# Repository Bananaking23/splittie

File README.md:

# splittie
I am going to design a board about 18.5x18.5mm in size, it will include leds, kailh switches and diodes, and i am going to create a split keyboard with it.

I made this project because every now and then i get the urge to create a new maccropad/keyboard with this pcb, i can create it in any shape or form and it is MUCH easier to wire then a handwired keyboard.
## Schematic

## Pcb

## Case

## BOM

| Part | Quantity | Price | Total price | Notes | Link |
|------|----------|-------|-------------|-------|------|
| PCB | | 17.02 | 18.52 | | [JLCPCB](https://jlcpcb.com) |
| Switches | 58 | 12.14 | 12.14 | | [AliExpress](https://www.aliexpress.com/item/1005006068116422.html) |
| Hotswap sockets | 58 | 5.92 | 5.92 | | [AliExpress](https://www.aliexpress.com/item/1005012056973371.html) |
| SK6812 MINI-E | 58 | 3.26 | 3.26 | optional | [AliExpress](https://www.aliexpress.com/item/1005005186515165.html) |
| Diodes | 58 | 1.15 | 1.15 | | [AliExpress](https://www.aliexpress.com/item/1005007160563285.html) |
| Keycaps | 1 set | 10.09 | 10.09 | | [AliExpress](https://www.aliexpress.com/item/1005011935100353.html) |
| RP2040 Pro Micro | 2 | 2.03 | 4.06 | | [AliExpress](https://www.aliexpress.com/item/1005009890367599.html) |
| 0.91" OLED | 2 | 2.07 | 2.07 | | [AliExpress](https://www.aliexpress.com/item/1005008640108394.html) |
| EC11 | 2 | 1.52 | 1.52 | | [AliExpress](https://www.aliexpress.com/item/1005007644083514.html) |
| USB-C female | 2 | 1.11 | 1.11 | connect 2 halves together | [AliExpress](https://www.aliexpress.com/item/1005008529430881.html) |
| USB-C cable | 1 | 3.19 | 3.19 | connect 2 halves together | [AliExpress](https://www.aliexpress.com/item/1005008570336761.html) |
| **Total** | | **63.03** | **77.72** | | |

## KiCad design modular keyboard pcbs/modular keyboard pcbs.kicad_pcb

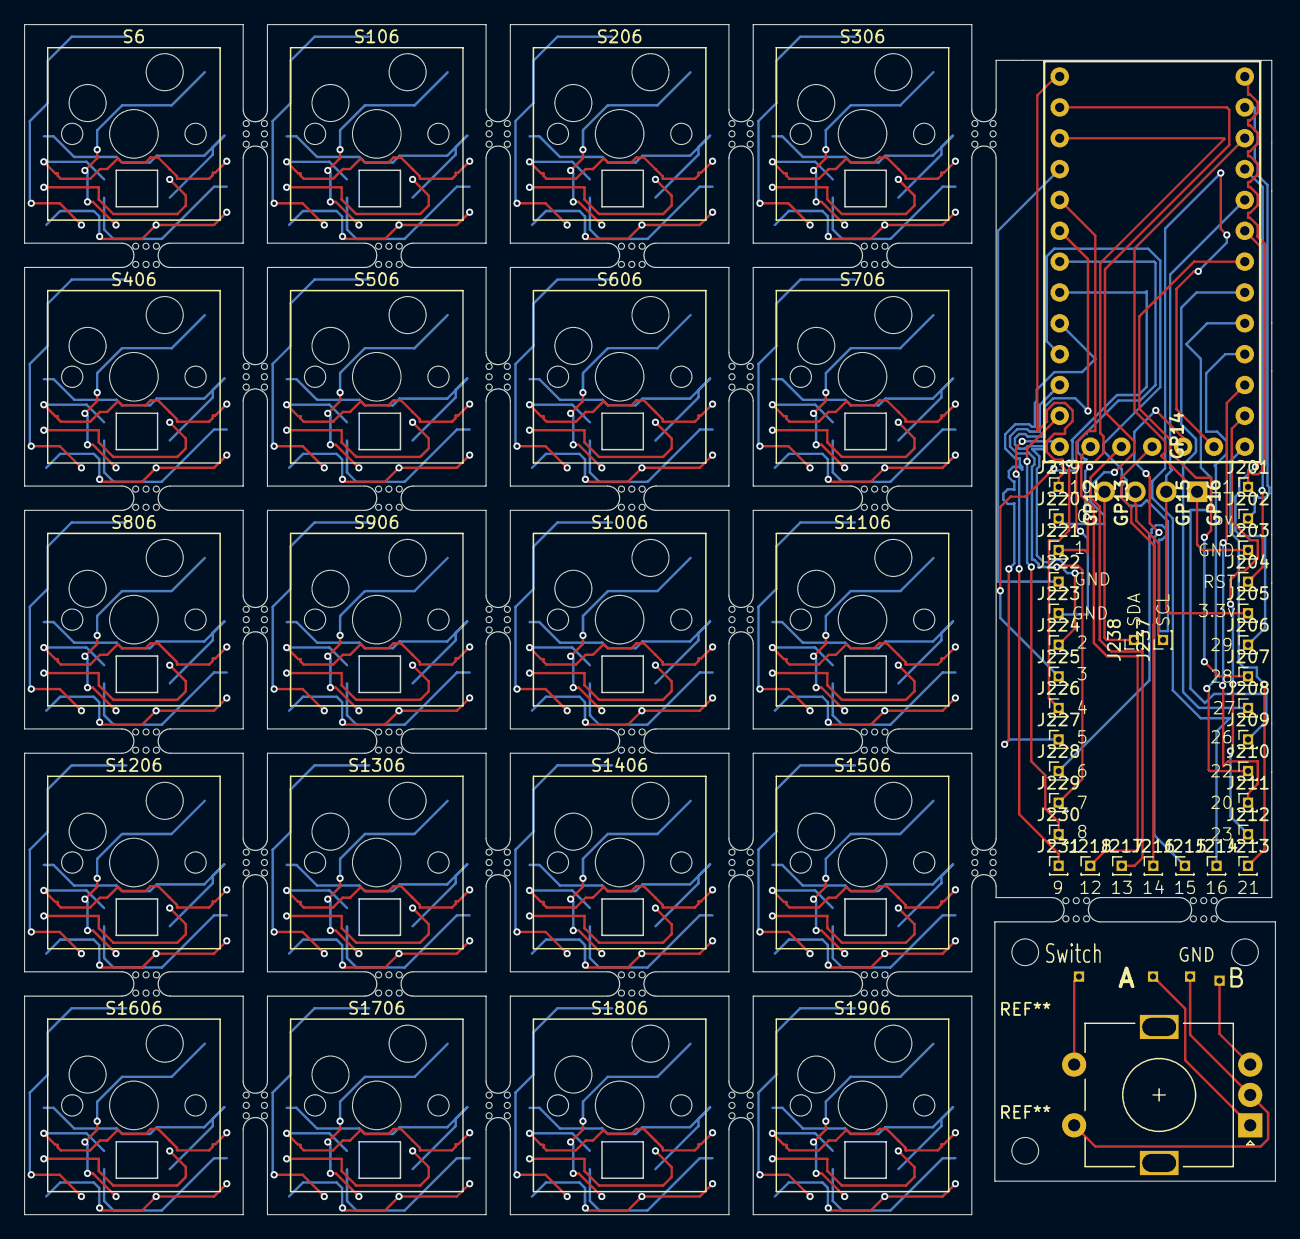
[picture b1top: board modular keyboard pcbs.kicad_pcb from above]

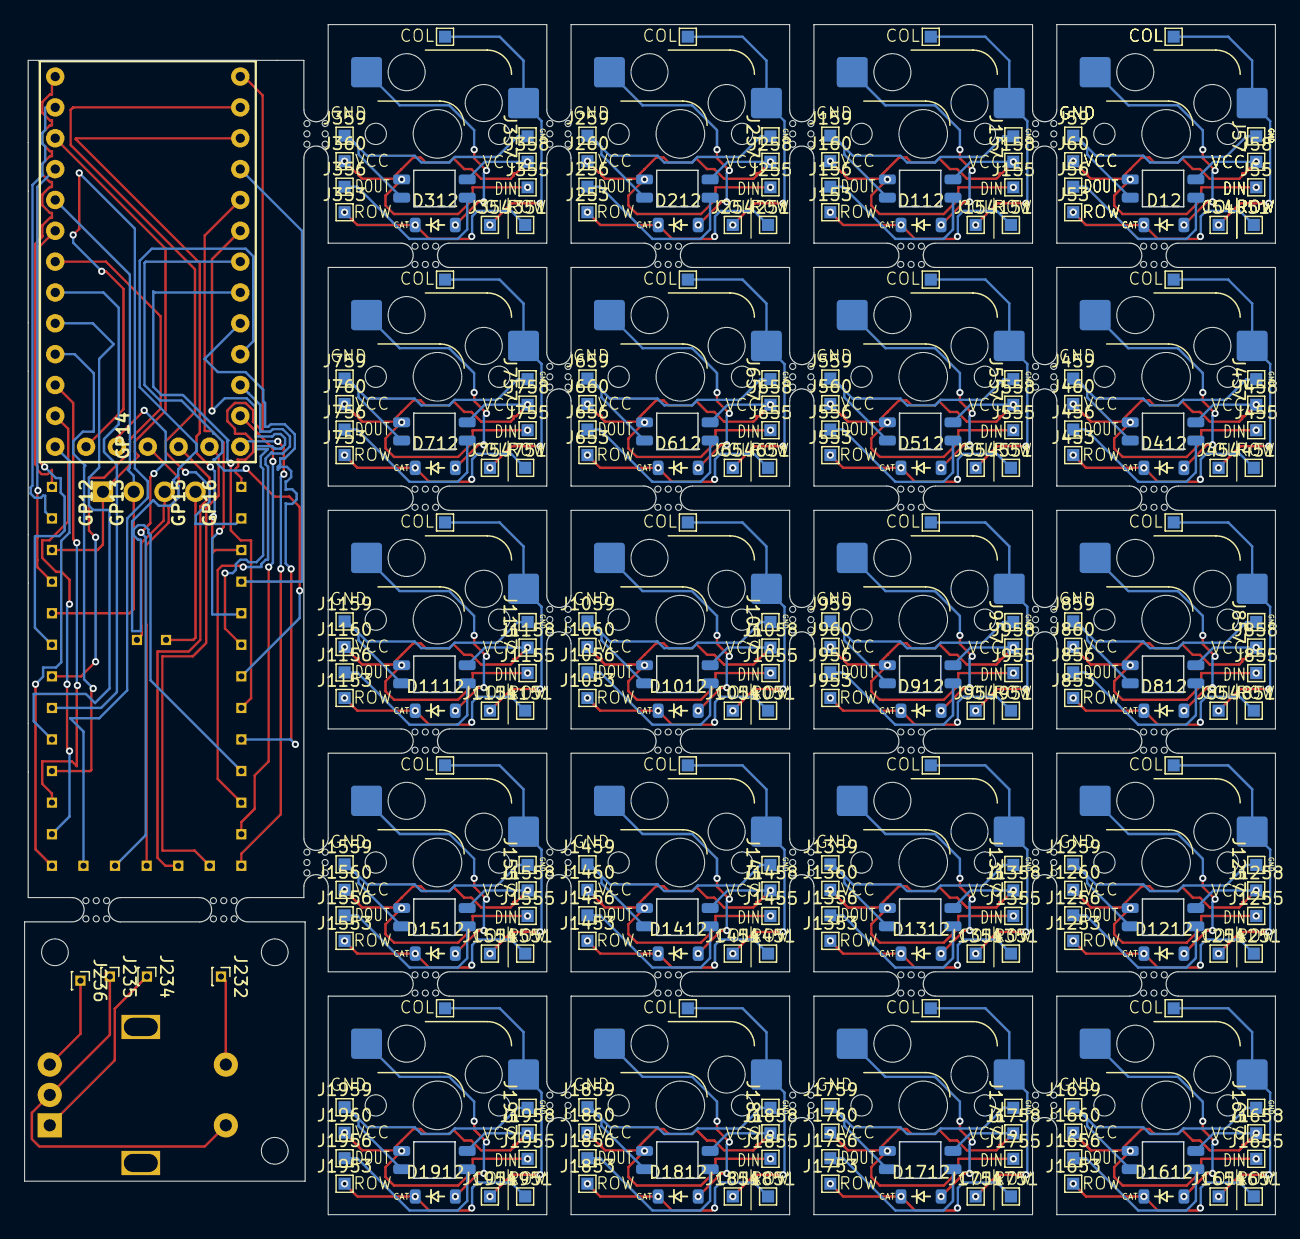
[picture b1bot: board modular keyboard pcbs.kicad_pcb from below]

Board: 2 copper layers, 103.0 x 98.0 mm, 300 parts (244 on the bottom side), 177 nets.

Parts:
D11, D111, D211, D311, D411, D511, D611, D711, D811, D911, D1011, D1111, D1211, D1311, D1411, D1511, D1611, D1711, D1811, D1911: LED_SK6812MINI
D12, D112, D212, D312, D412, D512, D612, D712, D812, D912, D1012, D1112, D1212, D1312, D1412, D1512, D1612, D1712, D1812, D1912: Diode_SOD-123
J51, J53, J151, J153, J251, J253, J351, J353, J451, J453, J551, J553, J651, J653, J751, J753, J851, J853, J951, J953, J1051, J1053, J1151, J1153, J1251, J1253, J1351, J1353, J1451, J1453, J1551, J1553, J1651, J1653, J1751, J1753, J1851, J1853, J1951, J1953: ROW; TestPoint_Pad_1.0x1.0mm
J52, J54, J152, J154, J252, J254, J352, J354, J452, J454, J552, J554, J652, J654, J752, J754, J852, J854, J952, J954, J1052, J1054, J1152, J1154, J1252, J1254, J1352, J1354, J1452, J1454, J1552, J1554, J1652, J1654, J1752, J1754, J1852, J1854, J1952, J1954: COL; TestPoint_Pad_1.0x1.0mm
J55, J155, J255, J355, J455, J555, J655, J755, J855, J955, J1055, J1155, J1255, J1355, J1455, J1555, J1655, J1755, J1855, J1955: DIN; TestPoint_Pad_1.0x1.0mm
J56, J156, J256, J356, J456, J556, J656, J756, J856, J956, J1056, J1156, J1256, J1356, J1456, J1556, J1656, J1756, J1856, J1956: DOUT; TestPoint_Pad_1.0x1.0mm
J57, J59, J157, J159, J257, J259, J357, J359, J457, J459, J557, J559, J657, J659, J757, J759, J857, J859, J957, J959, J1057, J1059, J1157, J1159, J1257, J1259, J1357, J1359, J1457, J1459, J1557, J1559, J1657, J1659, J1757, J1759, J1857, J1859, J1957, J1959: GND; TestPoint_Pad_1.0x1.0mm
J58, J60, J158, J160, J258, J260, J358, J360, J458, J460, J558, J560, J658, J660, J758, J760, J858, J860, J958, J960, J1058, J1060, J1158, J1160, J1258, J1260, J1358, J1360, J1458, J1460, J1558, J1560, J1658, J1660, J1758, J1760, J1858, J1860, J1958, J1960: VCC; TestPoint_Pad_1.0x1.0mm
J201, J202, J203, J204, J205, J206, J207, J208, J209, J210, J211, J212, J213, J214, J215, J216, J217, J218, J219, J220, J221, J222, J223, J224, J225, J226, J227, J228, J229, J230, J231, J232, J234, J235, J236, J237, J238: Conn_01x01_Pin; PinHeader_1x01_P1.00mm_Vertical
J233: OLED_128x32
S6, S106, S206, S306, S406, S506, S606, S706, S806, S906, S1006, S1106, S1206, S1306, S1406, S1506, S1606, S1706, S1806, S1906: Hotswap_MX_1.00u
SW1: RotaryEncoder_Switch; RotaryEncoder_Alps_EC11E-Switch_Vertical_H20mm
U1: RP2040_Pro_Micro

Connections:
/Cell r0c1/COL: J152.1, J154.1, S106.1
/Cell r0c1/DIN: D111.4 (DIN), J155.1
/Cell r0c1/DOUT: D111.2 (DOUT), J156.1
/Cell r0c1/GND: D111.3 (VSS), J157.1, J159.1
/Cell r0c1/Net-(D12-A): D112.2 (A), S106.2
/Cell r0c1/ROW: D112.1 (K), J151.1, J153.1
/Cell r0c1/VCC: D111.1 (VDD), J158.1, J160.1
/Cell r0c2/COL: J252.1, J254.1, S206.1
/Cell r0c2/DIN: D211.4 (DIN), J255.1
/Cell r0c2/DOUT: D211.2 (DOUT), J256.1
/Cell r0c2/GND: D211.3 (VSS), J257.1, J259.1
/Cell r0c2/Net-(D12-A): D212.2 (A), S206.2
/Cell r0c2/ROW: D212.1 (K), J251.1, J253.1
/Cell r0c2/VCC: D211.1 (VDD), J258.1, J260.1
/Cell r0c3/COL: J352.1, J354.1, S306.1
/Cell r0c3/DIN: D311.4 (DIN), J355.1
/Cell r0c3/DOUT: D311.2 (DOUT), J356.1
/Cell r0c3/GND: D311.3 (VSS), J357.1, J359.1
/Cell r0c3/Net-(D12-A): D312.2 (A), S306.2
/Cell r0c3/ROW: D312.1 (K), J351.1, J353.1
/Cell r0c3/VCC: D311.1 (VDD), J358.1, J360.1
/Cell r1c0/COL: J452.1, J454.1, S406.1
/Cell r1c0/DIN: D411.4 (DIN), J455.1
/Cell r1c0/DOUT: D411.2 (DOUT), J456.1
/Cell r1c0/GND: D411.3 (VSS), J457.1, J459.1
/Cell r1c0/Net-(D12-A): D412.2 (A), S406.2
/Cell r1c0/ROW: D412.1 (K), J451.1, J453.1
/Cell r1c0/VCC: D411.1 (VDD), J458.1, J460.1
/Cell r1c1/COL: J552.1, J554.1, S506.1
/Cell r1c1/DIN: D511.4 (DIN), J555.1
/Cell r1c1/DOUT: D511.2 (DOUT), J556.1
/Cell r1c1/GND: D511.3 (VSS), J557.1, J559.1
/Cell r1c1/Net-(D12-A): D512.2 (A), S506.2
/Cell r1c1/ROW: D512.1 (K), J551.1, J553.1
/Cell r1c1/VCC: D511.1 (VDD), J558.1, J560.1
/Cell r1c2/COL: J652.1, J654.1, S606.1
/Cell r1c2/DIN: D611.4 (DIN), J655.1
/Cell r1c2/DOUT: D611.2 (DOUT), J656.1
/Cell r1c2/GND: D611.3 (VSS), J657.1, J659.1
/Cell r1c2/Net-(D12-A): D612.2 (A), S606.2
/Cell r1c2/ROW: D612.1 (K), J651.1, J653.1
/Cell r1c2/VCC: D611.1 (VDD), J658.1, J660.1
/Cell r1c3/COL: J752.1, J754.1, S706.1
/Cell r1c3/DIN: D711.4 (DIN), J755.1
/Cell r1c3/DOUT: D711.2 (DOUT), J756.1
/Cell r1c3/GND: D711.3 (VSS), J757.1, J759.1
/Cell r1c3/Net-(D12-A): D712.2 (A), S706.2
/Cell r1c3/ROW: D712.1 (K), J751.1, J753.1
/Cell r1c3/VCC: D711.1 (VDD), J758.1, J760.1
/Cell r2c0/COL: J852.1, J854.1, S806.1
/Cell r2c0/DIN: D811.4 (DIN), J855.1
/Cell r2c0/DOUT: D811.2 (DOUT), J856.1
/Cell r2c0/GND: D811.3 (VSS), J857.1, J859.1
/Cell r2c0/Net-(D12-A): D812.2 (A), S806.2
/Cell r2c0/ROW: D812.1 (K), J851.1, J853.1
/Cell r2c0/VCC: D811.1 (VDD), J858.1, J860.1
/Cell r2c1/COL: J952.1, J954.1, S906.1
/Cell r2c1/DIN: D911.4 (DIN), J955.1
/Cell r2c1/DOUT: D911.2 (DOUT), J956.1
/Cell r2c1/GND: D911.3 (VSS), J957.1, J959.1
/Cell r2c1/Net-(D12-A): D912.2 (A), S906.2
/Cell r2c1/ROW: D912.1 (K), J951.1, J953.1
/Cell r2c1/VCC: D911.1 (VDD), J958.1, J960.1
/Cell r2c2/COL: J1052.1, J1054.1, S1006.1
/Cell r2c2/DIN: D1011.4 (DIN), J1055.1
/Cell r2c2/DOUT: D1011.2 (DOUT), J1056.1
/Cell r2c2/GND: D1011.3 (VSS), J1057.1, J1059.1
/Cell r2c2/Net-(D12-A): D1012.2 (A), S1006.2
/Cell r2c2/ROW: D1012.1 (K), J1051.1, J1053.1
/Cell r2c2/VCC: D1011.1 (VDD), J1058.1, J1060.1
/Cell r2c3/COL: J1152.1, J1154.1, S1106.1
/Cell r2c3/DIN: D1111.4 (DIN), J1155.1
/Cell r2c3/DOUT: D1111.2 (DOUT), J1156.1
/Cell r2c3/GND: D1111.3 (VSS), J1157.1, J1159.1
/Cell r2c3/Net-(D12-A): D1112.2 (A), S1106.2
/Cell r2c3/ROW: D1112.1 (K), J1151.1, J1153.1
/Cell r2c3/VCC: D1111.1 (VDD), J1158.1, J1160.1
/Cell r3c0/COL: J1252.1, J1254.1, S1206.1
/Cell r3c0/DIN: D1211.4 (DIN), J1255.1
/Cell r3c0/DOUT: D1211.2 (DOUT), J1256.1
/Cell r3c0/GND: D1211.3 (VSS), J1257.1, J1259.1
/Cell r3c0/Net-(D12-A): D1212.2 (A), S1206.2
/Cell r3c0/ROW: D1212.1 (K), J1251.1, J1253.1
/Cell r3c0/VCC: D1211.1 (VDD), J1258.1, J1260.1
/Cell r3c1/COL: J1352.1, J1354.1, S1306.1
/Cell r3c1/DIN: D1311.4 (DIN), J1355.1
/Cell r3c1/DOUT: D1311.2 (DOUT), J1356.1
/Cell r3c1/GND: D1311.3 (VSS), J1357.1, J1359.1
/Cell r3c1/Net-(D12-A): D1312.2 (A), S1306.2
/Cell r3c1/ROW: D1312.1 (K), J1351.1, J1353.1
/Cell r3c1/VCC: D1311.1 (VDD), J1358.1, J1360.1
/Cell r3c2/COL: J1452.1, J1454.1, S1406.1
/Cell r3c2/DIN: D1411.4 (DIN), J1455.1
/Cell r3c2/DOUT: D1411.2 (DOUT), J1456.1
/Cell r3c2/GND: D1411.3 (VSS), J1457.1, J1459.1
/Cell r3c2/Net-(D12-A): D1412.2 (A), S1406.2
/Cell r3c2/ROW: D1412.1 (K), J1451.1, J1453.1
/Cell r3c2/VCC: D1411.1 (VDD), J1458.1, J1460.1
/Cell r3c3/COL: J1552.1, J1554.1, S1506.1
/Cell r3c3/DIN: D1511.4 (DIN), J1555.1
/Cell r3c3/DOUT: D1511.2 (DOUT), J1556.1
/Cell r3c3/GND: D1511.3 (VSS), J1557.1, J1559.1
/Cell r3c3/Net-(D12-A): D1512.2 (A), S1506.2
/Cell r3c3/ROW: D1512.1 (K), J1551.1, J1553.1
/Cell r3c3/VCC: D1511.1 (VDD), J1558.1, J1560.1
/Cell r4c0/COL: J1652.1, J1654.1, S1606.1
/Cell r4c0/DIN: D1611.4 (DIN), J1655.1
/Cell r4c0/DOUT: D1611.2 (DOUT), J1656.1
/Cell r4c0/GND: D1611.3 (VSS), J1657.1, J1659.1
/Cell r4c0/Net-(D12-A): D1612.2 (A), S1606.2
/Cell r4c0/ROW: D1612.1 (K), J1651.1, J1653.1
/Cell r4c0/VCC: D1611.1 (VDD), J1658.1, J1660.1
/Cell r4c1/COL: J1752.1, J1754.1, S1706.1
/Cell r4c1/DIN: D1711.4 (DIN), J1755.1
/Cell r4c1/DOUT: D1711.2 (DOUT), J1756.1
/Cell r4c1/GND: D1711.3 (VSS), J1757.1, J1759.1
/Cell r4c1/Net-(D12-A): D1712.2 (A), S1706.2
/Cell r4c1/ROW: D1712.1 (K), J1751.1, J1753.1
/Cell r4c1/VCC: D1711.1 (VDD), J1758.1, J1760.1
/Cell r4c2/COL: J1852.1, J1854.1, S1806.1
/Cell r4c2/DIN: D1811.4 (DIN), J1855.1
/Cell r4c2/DOUT: D1811.2 (DOUT), J1856.1
/Cell r4c2/GND: D1811.3 (VSS), J1857.1, J1859.1
/Cell r4c2/Net-(D12-A): D1812.2 (A), S1806.2
/Cell r4c2/ROW: D1812.1 (K), J1851.1, J1853.1
/Cell r4c2/VCC: D1811.1 (VDD), J1858.1, J1860.1
/Cell r4c3/COL: J1952.1, J1954.1, S1906.1
/Cell r4c3/DIN: D1911.4 (DIN), J1955.1
/Cell r4c3/DOUT: D1911.2 (DOUT), J1956.1
/Cell r4c3/GND: D1911.3 (VSS), J1957.1, J1959.1
/Cell r4c3/Net-(D12-A): D1912.2 (A), S1906.2
/Cell r4c3/ROW: D1912.1 (K), J1951.1, J1953.1
/Cell r4c3/VCC: D1911.1 (VDD), J1958.1, J1960.1
/Switch cell5/COL: J52.1, J54.1, S6.1
/Switch cell5/DIN: D11.4 (DIN), J55.1
/Switch cell5/DOUT: D11.2 (DOUT), J56.1
/Switch cell5/GND: D11.3 (VSS), J57.1, J59.1
/Switch cell5/ROW: D12.1 (K), J51.1, J53.1
/Switch cell5/VCC: D11.1 (VDD), J58.1, J60.1
unnamed: D12.2 (A), S6.2
unnamed: J201.1, U1.31 (GP11)
unnamed: J202.1, U1.30 (5v)
unnamed: J203.1, J233.1 (GND), U1.29 (GND)
unnamed: J204.1, U1.28 (RST)
unnamed: J205.1, J233.2 (VCC), U1.27 (3.3v)
unnamed: J206.1, U1.26 (GP29)
unnamed: J207.1, U1.25 (GP28)
unnamed: J208.1, U1.24 (GP27)
unnamed: J209.1, U1.23 (GP26)
unnamed: J210.1, U1.22 (GP22)
unnamed: J211.1, U1.21 (GP20)
unnamed: J212.1, U1.20 (GP23)
unnamed: J213.1, U1.19 (GP21)
unnamed: J214.1, U1.18 (GP16)
unnamed: J215.1, U1.17 (GP15)
unnamed: J216.1, U1.16 (GP14)
unnamed: J217.1, U1.15 (GP13)
unnamed: J218.1, U1.14 (GP12)
unnamed: J219.1, U1.1 (GP10)
unnamed: J220.1, U1.2 (GP0)
unnamed: J221.1, U1.3 (GP1)
unnamed: J222.1, U1.4 (GND)
unnamed: J223.1, U1.5 (GND)
unnamed: J224.1, U1.6 (GP2)
unnamed: J225.1, U1.7 (GP3)
unnamed: J226.1, U1.8 (GP4)
unnamed: J227.1, U1.9 (GP5)
unnamed: J228.1, U1.10 (GP6)
unnamed: J229.1, U1.11 (GP7)
unnamed: J230.1, U1.12 (GP8)
unnamed: J231.1, U1.13 (GP9)
unnamed: J232.1, SW1.S1
unnamed: J233.3 (SCL), J237.1
unnamed: J233.4 (SDA), J238.1
unnamed: J234.1, SW1.A
unnamed: J235.1, SW1.C, SW1.S2
unnamed: J236.1, SW1.B

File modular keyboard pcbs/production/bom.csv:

Designator,Footprint,Quantity,Value,LCSC Part #
"D1011, D11, D111, D1111, D1211, D1311, D1411, D1511, D1611, D1711, D1811, D1911, D211, D311, D411, D511, D611, D711, D811, D911",LED_SK6812MINI,20,LED_SK6812MINI,C5149201
"D1012, D1112, D112, D12, D1212, D1312, D1412, D1512, D1612, D1712, D1812, D1912, D212, D312, D412, D512, D612, D712, D812, D912",Diode_SOD-123,20,~,
"J1051, J1053, J1151, J1153, J1251, J1253, J1351, J1353, J1451, J1453, J151, J153, J1551, J1553, J1651, J1653, J1751, J1753, J1851, J1853, J1951, J1953, J251, J253, J351, J353, J451, J453, J51, J53, J551, J553, J651, J653, J751, J753, J851, J853, J951, J953",TestPoint_Pad_1.0x1.0mm,40,ROW,
"J1052, J1054, J1152, J1154, J1252, J1254, J1352, J1354, J1452, J1454, J152, J154, J1552, J1554, J1652, J1654, J1752, J1754, J1852, J1854, J1952, J1954, J252, J254, J352, J354, J452, J454, J52, J54, J552, J554, J652, J654, J752, J754, J852, J854, J952, J954",TestPoint_Pad_1.0x1.0mm,40,COL,
"J1055, J1155, J1255, J1355, J1455, J155, J1555, J1655, J1755, J1855, J1955, J255, J355, J455, J55, J555, J655, J755, J855, J955",TestPoint_Pad_1.0x1.0mm,20,DIN,
"J1056, J1156, J1256, J1356, J1456, J1556, J156, J1656, J1756, J1856, J1956, J256, J356, J456, J556, J56, J656, J756, J856, J956",TestPoint_Pad_1.0x1.0mm,20,DOUT,
"J1057, J1059, J1157, J1159, J1257, J1259, J1357, J1359, J1457, J1459, J1557, J1559, J157, J159, J1657, J1659, J1757, J1759, J1857, J1859, J1957, J1959, J257, J259, J357, J359, J457, J459, J557, J559, J57, J59, J657, J659, J757, J759, J857, J859, J957, J959",TestPoint_Pad_1.0x1.0mm,40,GND,
"J1058, J1060, J1158, J1160, J1258, J1260, J1358, J1360, J1458, J1460, J1558, J1560, J158, J160, J1658, J1660, J1758, J1760, J1858, J1860, J1958, J1960, J258, J260, J358, J360, J458, J460, J558, J560, J58, J60, J658, J660, J758, J760, J858, J860, J958, J960",TestPoint_Pad_1.0x1.0mm,40,VCC,
"J201, J202, J203, J204, J205, J206, J207, J208, J209, J210, J211, J212, J213, J214, J215, J216, J217, J218, J219, J220, J221, J222, J223, J224, J225, J226, J227, J228, J229, J230, J231, J232, J234, J235, J236, J237, J238",PinHeader_1x01_P1.00mm_Vertical,37,Conn_01x01_Pin,
J233,OLED_128x32,1,OLED_128x32,
"S1006, S106, S1106, S1206, S1306, S1406, S1506, S1606, S1706, S1806, S1906, S206, S306, S406, S506, S6, S606, S706, S806, S906",Hotswap_MX_1.00u,20,~,
SW1,RotaryEncoder_Alps_EC11E-Switch_Vertical_H20mm,1,RotaryEncoder_Switch,
U1,RP2040_Pro_Micro,1,RP2040_Pro_Micro,
